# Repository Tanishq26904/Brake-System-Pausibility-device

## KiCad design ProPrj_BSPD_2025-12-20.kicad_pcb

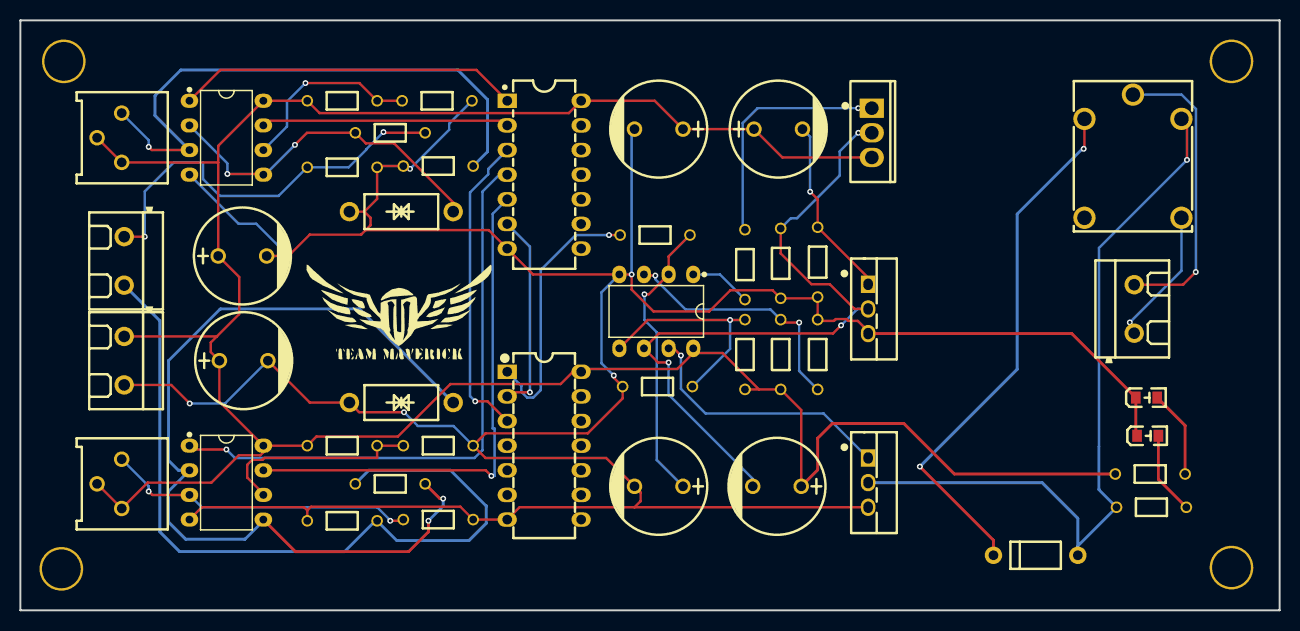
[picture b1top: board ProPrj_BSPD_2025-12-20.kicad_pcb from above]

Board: 2 copper layers, 129.8 x 60.8 mm, 45 parts (0 on the bottom side), 31 nets.

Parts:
A1: PDIP-14_L19.3-W6.4-P2.54-LS7.9-BL-1
A2: PDIP-14_L19.3-W6.5-P2.54-LS7.6-BL
FC1, FC2, FC3: CAP-TH_BD10.0-P5.00-D0.6-FD
FD1: DO-41_BD2.4-L4.7-P8.70-D0.9-RD
NM1, NM2: TO-220-3_L10.2-W4.5-P2.54-L-1
O1, O2, O3: DIP-8_L9.4-W6.4-P2.54-LS9.1-BL
OK1: LED0805-RD_GREEN
P1, P2, P3: CONN-TH_XY301V-A-5.0-2P
PM1: TO-220AB-3_L10.4-W4.6-P2.54-L
POW1: LED0805-RD_GREEN
R0, R1, R2, R3, R4, R5, R6, R7, R8, R9, R10, R11, R12, R13, R14, R15, R16, R17, R18, R19: RES-TH_BD1.8-L3.2-P7.20-D0.4
R21: RELAY-TH_YA-SS-105D
TC1, TC2, TC3: CAP-TH_BD10.0-P5.00-D0.6-FD
TVSD1, TVSD2: DO-15_BD3.1-L6.7-P10.70-D0.8-BI
VR1, VR2: RES-ADJ-TH_3P-L9.5-W9.5-P2.54-BR-BS

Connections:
$1N3604: O1.6, R4.2, R5.1
$1N3611: O3.5, R15.2, R16.1
$1N3615: O3.3, R12.2, R13.1
$1N3616: O3.2, R11.1, TC1.1
$1N3617: A1.1, O1.1
$1N3618: O1.2, O1.5, R2.1, TVSD1.2
$1N3619: O1.3, R3.1, VR1.3
$1N3620: A1.2, O1.7
$1N3621: O2.3, R8.1, VR2.3
$1N3622: A1.6, A2.2
$1N3623: A1.3, A2.3
$1N3628: O3.1, R14.1
$1N3629: PM1.1, R14.2
$1N3631: A2.1, R11.2
$1N3635: A1.4, O2.1
$1N3636: O2.6, R9.2, R10.1
$1N3637: O2.2, O2.5, R7.1, TVSD2.2
$1N3638: A1.5, O2.7
$1N3655: NM1.2, O3.6, PM1.2, R17.1, TC2.2
$1N3660: NM1.1, R18.1, TC3.2
$1N3662: NM2.1, O3.7
$1N4005: FD1.2, NM2.2, R19.2, R21.5
$1N4105: POW1.2, R0.2
$1N4127: OK1.2, R19.1
+5V: A1.14, A2.14, FC1.1, FC2.1, FC3.1, O1.8, O2.8, O3.8, P2.2, PM1.3, R0.1, R4.1, R9.1, R12.1, R15.1, TC2.1, TC3.1, VR1.1, VR1.2, VR2.1, VR2.2
GND: A1.7, A2.7, FC1.2, FC2.2, FC3.2, NM1.3, NM2.3, O1.4, O2.4, O3.4, OK1.1, P2.1, POW1.1, R1.2, R3.2, R5.2, R6.2, R8.2, R10.2, R13.2, R16.2, R17.2, R18.2, TC1.2, TVSD1.1, TVSD2.1
SC_IN: P3.1, R21.2
SC_OUT: P3.2, R21.4
SEN1: P1.2, R1.1, R2.2
SEN2: P1.1, R6.1, R7.2
VCC: FD1.1, R21.1

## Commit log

2025-12-19 plot file
2025-12-19 plot file colour
2025-12-19 pcb border layer change
